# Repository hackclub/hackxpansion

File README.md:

<h1 align="center">
    Hackxpansion
</h1>

<h3 align="center">
    <a href="https://hackxpansion.koeg.dev">Website</a>
    <br/>
</h3>

<h4 align="center">
    A handheld console with 4 expansion solts
</h4>

<div align="center">
    
</div>

## Key Features

- Resistor based module identification at start up
- [2" 240x320 ST7789 LCD panel](https://www.buydisplay.com/2-inch-ips-tft-lcd-display-ips-panel-screen-240x320-for-smart-watch)
- RP2354 MCU
- Easily adaptable [module standard](https://hackxpansion.dino.icu/docs/detailed/card)
- Rust firmware with [embassy](https://embassy.dev/) and [slint-ui](https://slint.dev/)

## Why?

I really like the idea of modules, and modular things, and making people work together, so I made this.

## PCB

The console has two 4 layer PCBs designed in KiCAD, a main-board and a daughter-board, designed for JLC's basic process. 

### Main-Board

### Daughter-Board

## Making Your Own Modules

There are three simple steps to making your own module:

1. Design the module PCB in KiCAD
2. Design the module case in CAD
3. Write a driver for the module

There are detailed docs on the [hackxpansion website](https://hackxpansion.dino.icu/docs)

## Case

The case is designed in Autodesk Fusion, there are .f3z files in the hardware directory.

The models have parameters that can be adjusted to fit your needs.

## Shoutouts

Thank you so much for [Simon](https://github.com/NEOgHacking) who helped with the fanout of the RP, and also gave a ton of constructive feedback!!!!

## Zine

## BOM for Console

This is for an order of 2 PCBA PCBs.

Also found in a [CSV file](hardware/hackxpansion/BOM.csv). Each component has an LCSC part number attached that can be used to find the component on the LCSC website.

|Item                      |Price per unit|Nr of units|Total price|Link                                                                                          |
|--------------------------|--------------|-----------|-----------|----------------------------------------------------------------------------------------------|
|PCB with PCBA             |$60.00        |1          |$60.00     |https://jlcpcb.com/                                                                           |
|Display                   |$4.36         |1          |$4.36      |https://www.buydisplay.com/2-inch-ips-tft-lcd-display-ips-panel-screen-240x320-for-smart-watch|
|2x7 2.54mm header         |$0.386        |10         |$3.860     |https://www.aliexpress.com/item/1005012166781874.html                                         |
|Battery 502035            |$6.64         |1          |$6.64      |https://www.aliexpress.com/item/1005008218024646.html                                         |
|M2 OD3 L2 heat set insert |$0.0696       |15         |$1.0440    |https://www.aliexpress.com/item/1005006798286851.html                                         |
|M2 L6 screw               |$0.0766       |5          |$0.3830    |https://www.aliexpress.com/item/4000970993800.html                                            |
|M2 L8 screw               |$0.0766       |2          |$0.1532    |https://www.aliexpress.com/item/4000970993800.html                                            |
|M2 L4 screw               |$0.0766       |8          |$0.6128    |https://www.aliexpress.com/item/4000970993800.html                                            |
|                          |              |Total:     |$77.05     |                                                                                              |

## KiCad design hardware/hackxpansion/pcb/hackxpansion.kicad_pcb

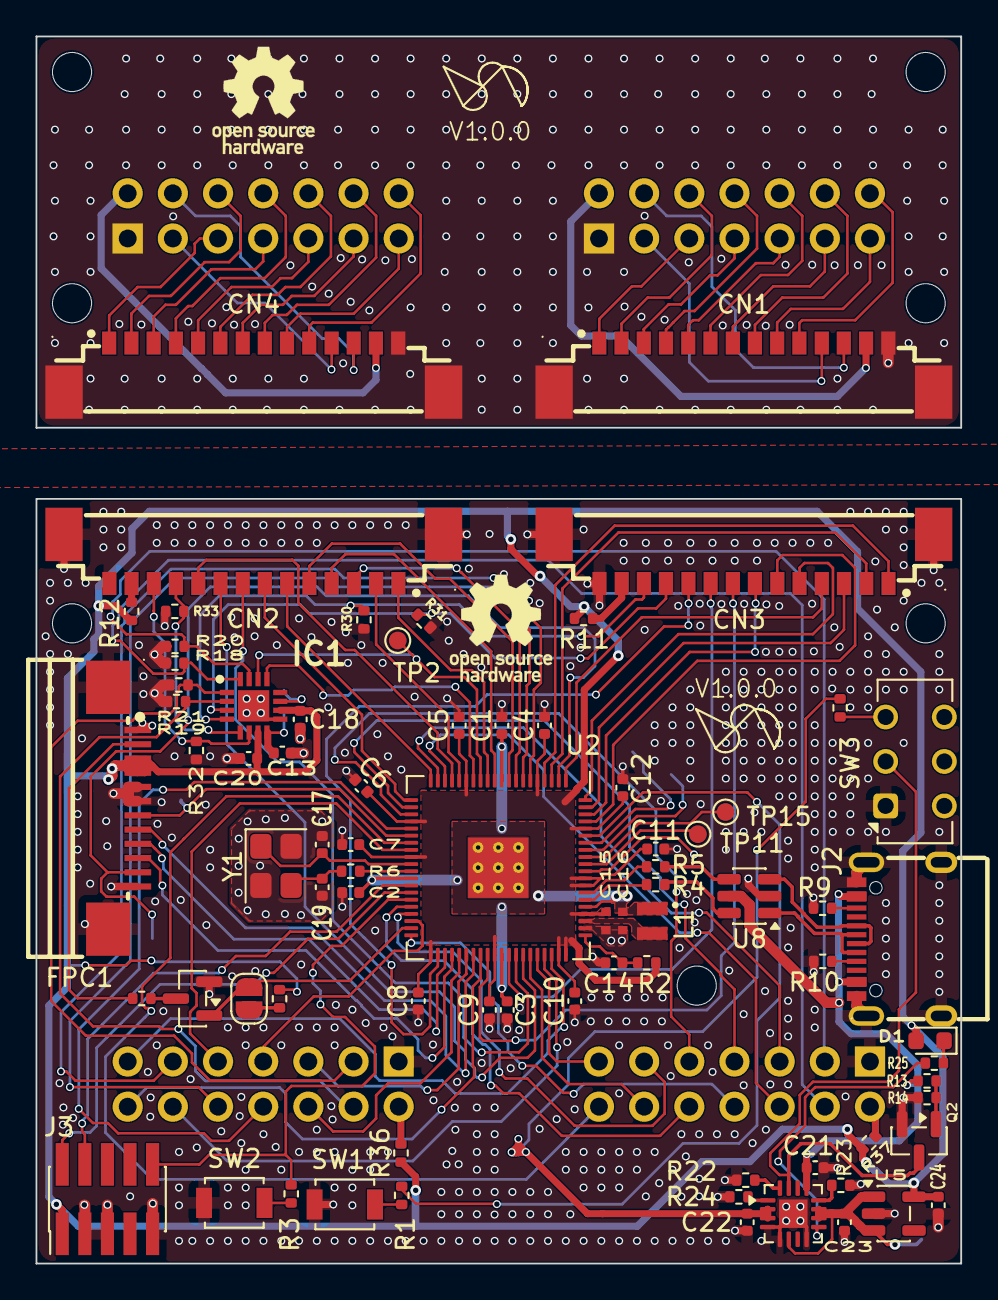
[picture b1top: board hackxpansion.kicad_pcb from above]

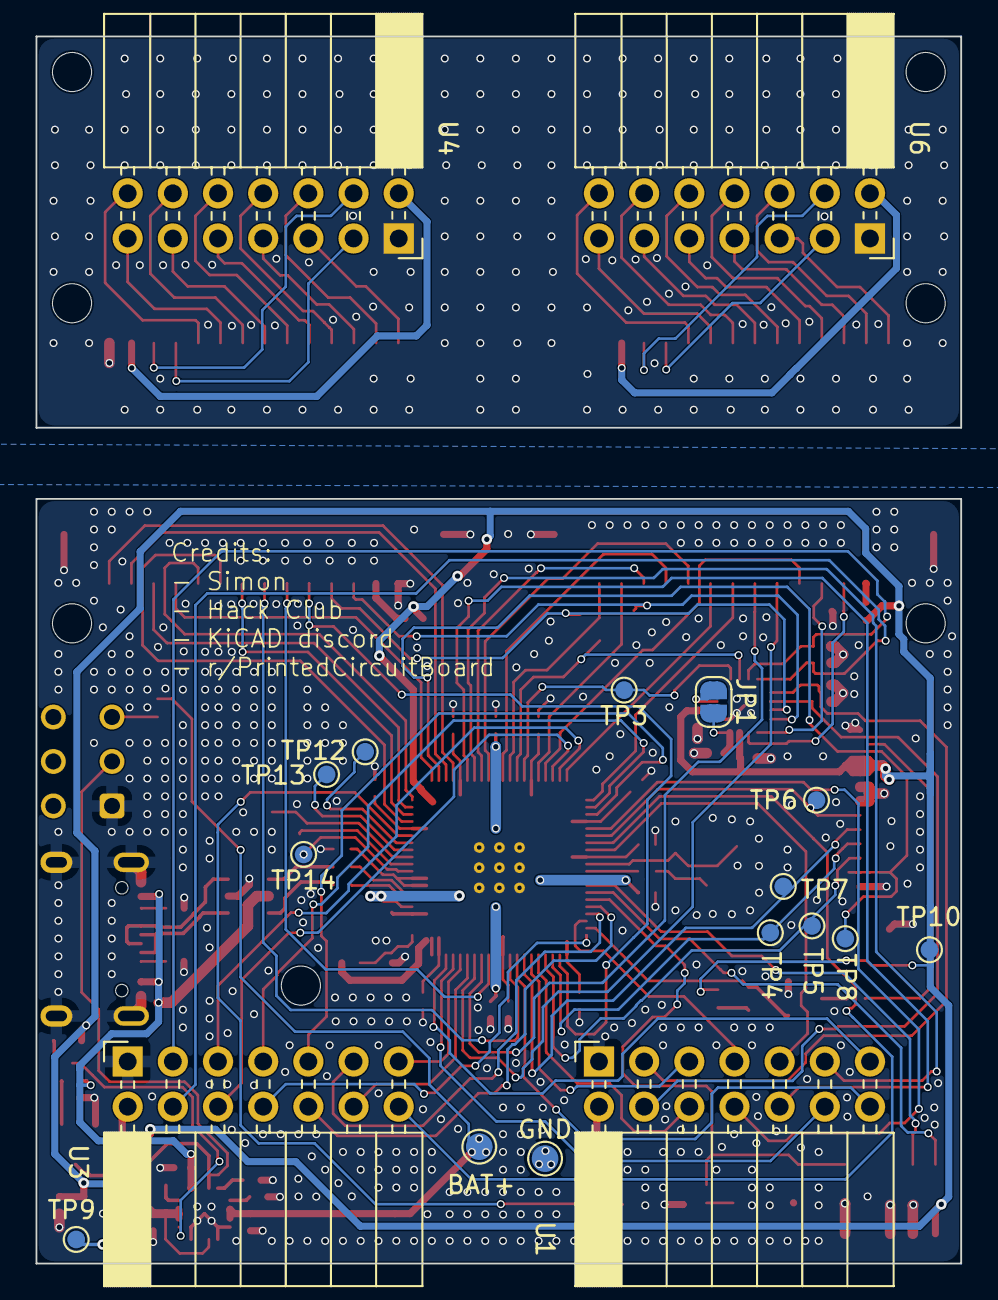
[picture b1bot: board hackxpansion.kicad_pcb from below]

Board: 4 copper layers, 52.0 x 43.0 mm, 104 parts (21 on the bottom side), 130 nets.

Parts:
BAT+: TestPoint; TestPoint_Pad_D1.5mm
C1, C3, C4, C5, C6, C7, C8, C9, C10, C11, C12: 100n; C_0402_1005Metric
C2, C14, C21, C22, C23, C24: 4u7; C_0402_1005Metric
C13, C18, C20: 1u; C_0402_1005Metric
C15, C16: 4u7; C_0402_1005Metric_small_pads
C17, C19: 15p; C_0402_1005Metric
CN1, CN2, CN3, CN4: 533981471; CONN-SMD_14P-P1.25_MOLEX_533981471
D1: LED; LED_0603_1608Metric
FPC1: AFC08-S12ECA-00; FPC-SMD_P0.80-12P_LCS-SJ-H2.0
GND: TestPoint; TestPoint_Pad_D1.5mm
H1, H2, H3, H4, H5, H6, H7: MountingHole; MountingHole_2.2mm_M2
IC1: ADS7128IRTET; QFN50P300X300X80-17N-D
J2: USB_C_Receptacle_USB2.0_14P; USB-C-SMD_TYPE-C-16PIN-2MD-073
J3: Conn_ARM_JTAG_SWD_10; PinHeader_2x05_P1.27mm_Vertical_SMD
JP1, JP3: SolderJumper_2_Open; SolderJumper-2_P1.3mm_Open_RoundedPad1.0x1.5mm
L1: 3u3; L_pol_2016
Q1: BSS138; SOT-23
Q2: 2N7002; SOT-23
R1, R3, R6: 1k; R_0402_1005Metric
R2: 33R; R_0402_1005Metric
R4, R5: 27R; R_0402_1005Metric
R7: 10R; R_0402_1005Metric
R8, R14, R18, R19, R20, R21, R24, R30, R31, R32, R33: 10k; R_0402_1005Metric
R9, R10: 5k1; R_0402_1005Metric
R11, R12, R36, R37: 5R1; R_0402_1005Metric
R13: 100R; R_0402_1005Metric
R15: 100k; R_0402_1005Metric
R22: 3k3; R_0402_1005Metric
R23, R25: 1k5; R_0402_1005Metric
SW1, SW2: SW_Push; SW_SPST_B3U-1000P
SW3: SW_On_Off; SW_CK_JS202011AQN_DPDT_Angled
SYM1, SYM2: Logo_Open_Hardware_Small; OSHW-Logo_5.7x6mm_SilkScreen
TP2, TP3, TP4, TP5, TP6, TP7, TP8, TP9, TP10, TP11, TP12, TP13, TP14, TP15: TestPoint; TestPoint_Pad_D1.0mm
U1, U3, U4, U6: PinSocket_2x07_P2.54mm_Horizontal
U2: RP2354B; RP2350-QFN-80-1EP_10x10_P0.4mm_EP3.4x3.4mm_ThermalVias
U5: SPX3819M5-L-3-3; SOT-23-5
U7: BQ24075RGT; VQFN-16-1EP_3x3mm_P0.5mm_EP1.6x1.6mm
U8: USBLC6-2SC6; SOT-23-6
Y1: ABM8-272-T3; Crystal_SMD_3225-4Pin_3.2x2.5mm

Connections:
+1V1: C1.1, C2.1, C3.1, C16.1, L1.1, U2.10 (DVDD), U2.32 (DVDD), U2.51 (DVDD), U2.65 (VREG_FB)
/+3V3: C4.1, C5.1, C6.1, C7.1, C8.1, C9.1, C10.1, C11.1, C12.1, C15.1, C18.1, C20.1, C24.2, D1.2 (A), FPC1.3, FPC1.4, IC1.7 (AVDD), IC1.10 (DVDD), J3.1 (VTref), R2.1, R8.2, R11.1, R12.1, R36.1, R37.1, TP10.1 (1_1), U2.5 (IOVDD), U2.15 (IOVDD), U2.24 (IOVDD), U2.29 (IOVDD), U2.41 (IOVDD), U2.50 (IOVDD), U2.59 (ADC_AVDD), U2.60 (IOVDD), U2.64 (VREG_VIN), U2.68 (USB_OTP_VDD), U2.69 (QSPI_IOVDD), U2.76 (IOVDD), U5.5 (OUT)
/Connector Daughter Mod2/bank.GPIO0: CN1.1, U4.5 (GPIO0)
/Connector Daughter Mod2/bank.GPIO1: CN1.2, U4.6 (GPIO1)
/Connector Daughter Mod2/bank.GPIO2: CN1.3, U4.7 (GPI02)
/Connector Daughter Mod2/bank.GPIO3: CN1.4, U4.8 (GPIO3)
/Connector Daughter Mod2/bank.GPIO4: CN1.5, U4.9 (GPIO4)
/Connector Daughter Mod2/bank.GPIO5: CN1.6, U4.10 (GPIO5)
/Connector Daughter Mod2/bank.GPIO6: CN1.7, U4.11 (GPIO6)
/Connector Daughter Mod2/bank.GPIO7: CN1.8, U4.12 (GPIO7)
/Connector Daughter Mod2/bank.GPIO8: CN1.9, U4.13 (GPIO8)
/Connector Daughter Mod2/bank.GPIO9: CN1.10, U4.14 (GPIO9)
/Connector Daughter Mod2/mod.MD0: CN1.11, U4.3 (MD0)
/Connector Daughter Mod2/mod.MD1: CN1.12, U4.4 (MD1)
/Connector Daughter Mod3/bank.GPIO0: CN4.1, U6.5 (GPIO0)
/Connector Daughter Mod3/bank.GPIO1: CN4.2, U6.6 (GPIO1)
/Connector Daughter Mod3/bank.GPIO2: CN4.3, U6.7 (GPI02)
/Connector Daughter Mod3/bank.GPIO3: CN4.4, U6.8 (GPIO3)
/Connector Daughter Mod3/bank.GPIO4: CN4.5, U6.9 (GPIO4)
/Connector Daughter Mod3/bank.GPIO5: CN4.6, U6.10 (GPIO5)
/Connector Daughter Mod3/bank.GPIO6: CN4.7, U6.11 (GPIO6)
/Connector Daughter Mod3/bank.GPIO7: CN4.8, U6.12 (GPIO7)
/Connector Daughter Mod3/bank.GPIO8: CN4.9, U6.13 (GPIO8)
/Connector Daughter Mod3/bank.GPIO9: CN4.10, U6.14 (GPIO9)
/Connector Daughter Mod3/mod.MD0: CN4.11, U6.3 (MD0)
/Connector Daughter Mod3/mod.MD1: CN4.12, U6.4 (MD1)
/Connector Main Mod2/+3V3: CN3.13, R11.2
/Connector Main Mod2/bank.GPIO0: CN3.1, U2.4 (GPIO7)
/Connector Main Mod2/bank.GPIO1: CN3.2, U2.3 (GPIO6)
/Connector Main Mod2/bank.GPIO2: CN3.3, U2.79 (GPIO2)
/Connector Main Mod2/bank.GPIO3: CN3.4, U2.1 (GPIO4)
/Connector Main Mod2/bank.GPIO4: CN3.5, U2.80 (GPIO3)
/Connector Main Mod2/bank.GPIO5: CN3.6, U2.77 (GPIO0)
/Connector Main Mod2/bank.GPIO6: CN3.7, U2.78 (GPIO1)
/Connector Main Mod2/bank.GPIO7: CN3.8, U2.49 (GPIO40/ADC0)
/Connector Main Mod2/bank.GPIO8: CN3.9, U2.52 (GPIO41/ADC1)
/Connector Main Mod2/bank.GPIO9: CN3.10, U2.42 (GPIO33)
/Connector Main Mod2/mod.MD0: CN3.11, IC1.3 (AIN4/GPIO4), R31.1
/Connector Main Mod2/mod.MD1: CN3.12, IC1.4 (AIN5/GPIO5), R30.1
/Connector Main Mod3/+3V3: CN2.13, R12.2
/Connector Main Mod3/bank.GPIO0: CN2.1, U2.12 (GPIO13)
/Connector Main Mod3/bank.GPIO1: CN2.2, U2.16 (GPIO16)
/Connector Main Mod3/bank.GPIO2: CN2.3, U2.8 (GPIO10)
/Connector Main Mod3/bank.GPIO3: CN2.4, U2.11 (GPIO12)
/Connector Main Mod3/bank.GPIO4: CN2.5, U2.9 (GPIO11)
/Connector Main Mod3/bank.GPIO5: CN2.6, U2.20 (GPIO20)
/Connector Main Mod3/bank.GPIO6: CN2.7, U2.21 (GPIO21)
/Connector Main Mod3/bank.GPIO7: CN2.8, U2.53 (GPIO42/ADC2)
/Connector Main Mod3/bank.GPIO8: CN2.9, U2.54 (GPIO43/ADC3)
/Connector Main Mod3/bank.GPIO9: CN2.10, U2.17 (GPIO17)
/Connector Main Mod3/mod.MD0: CN2.11, IC1.5 (AIN6/GPIO6), R33.1
/Connector Main Mod3/mod.MD1: CN2.12, IC1.6 (AIN7/GPIO7), R32.1
/DAUGHT_GND: CN1.14, CN1.15, CN1.16, CN4.14, CN4.15, CN4.16, U4.1 (GND), U6.1 (GND)
/Daughter Board/+3V3_MOD2: CN1.13, U4.2 (3V3)
/Daughter Board/+3V3_MOD3: CN4.13, U6.2 (3V3)
/GND: C1.2, C2.2, C3.2, C4.2, C5.2, C6.2, C7.2, C8.2, C9.2, C10.2, C11.2, C12.2, C13.2, C14.2, C15.2, C16.2, C17.1, C18.2, C19.1, C20.2, C21.1, C22.1, C23.1, C24.1, CN2.14, CN2.15, CN2.16, CN3.14, CN3.15, CN3.16, FPC1.1, FPC1.5, FPC1.6, FPC1.12, FPC1.13, FPC1.14, GND.1 (1_1), IC1.9 (GND), IC1.17 (EP), J2.A1 (GND), J2.A12 (GND), J2.B1 (GND), J2.B12 (GND), J2.SH (SHIELD), J3.3 (GND), J3.5 (GND), J3.9 (GNDDetect), Q1.2 (S), Q2.2 (S), R9.2, R10.2, R14.2, R18.2, R19.2, R20.2, R21.2, R22.2, R23.2, R24.2, R30.2, R31.2, R32.2, R33.2, SW1.1, SW2.1, SW3.1 (A), U1.1 (GND), U2.62 (VREG_PGND), U2.81 (GND), U3.1 (GND), U5.2 (GND), U7.4 (~CE), U7.5 (EN2), U7.8 (VSS), U7.17 (VSS), U8.2 (GND), Y1.2 (G), Y1.4 (G)
/Main Board/ADC/SCL: IC1.13 (SCL), TP3.1 (1_1), U2.14 (GPIO15)
/Main Board/ADC/SDA: IC1.14 (SDA), TP2.1 (1_1), U2.13 (GPIO14)
/Main Board/ADC/mod0.MD0: IC1.1 (AIN2/GPIO2), R21.1, U1.3 (MD0)
/Main Board/ADC/mod0.MD1: IC1.2 (AIN3/GPIO3), R19.1, U1.4 (MD1)
/Main Board/ADC/mod1.MD0: IC1.15 (AIN0/GPIO0), R20.1, U3.3 (MD0)
/Main Board/ADC/mod1.MD1: IC1.16 (AIN1/GPIO1), R18.1, U3.4 (MD1)
/Main Board/Display/BACKLIGHT: JP3.2 (B), Q1.1 (G), U2.39 (GPIO31)
/Main Board/Display/CS: FPC1.8, TP7.1 (1_1), U2.47 (GPIO38)
/Main Board/Display/DC: FPC1.7, TP6.1 (1_1), U2.26 (GPIO25)
/Main Board/Display/MOSI: FPC1.10, TP5.1 (1_1), U2.44 (GPIO35)
/Main Board/Display/RESET: FPC1.11, TP8.1 (1_1), U2.2 (GPIO5)
/Main Board/Display/SCLK: FPC1.9, TP4.1 (1_1), U2.43 (GPIO34)
/Main Board/Module Bay 0/+3V3: R36.2, U1.2 (3V3)
/Main Board/Module Bay 0/GPIO0: U1.5 (GPIO0), U2.46 (GPIO37)
/Main Board/Module Bay 0/GPIO1: U1.6 (GPIO1), U2.45 (GPIO36)
/Main Board/Module Bay 0/GPIO2: U1.7 (GPI02), U2.38 (GPIO30)
/Main Board/Module Bay 0/GPIO3: U1.8 (GPIO3), U2.25 (GPIO24)
/Main Board/Module Bay 0/GPIO4: U1.9 (GPIO4), U2.28 (GPIO27)
/Main Board/Module Bay 0/GPIO5: U1.10 (GPIO5), U2.6 (GPIO8)
/Main Board/Module Bay 0/GPIO6: U1.11 (GPIO6), U2.7 (GPIO9)
/Main Board/Module Bay 0/GPIO7: U1.12 (GPIO7), U2.57 (GPIO46/ADC6)
/Main Board/Module Bay 0/GPIO8: U1.13 (GPIO8), U2.58 (GPIO47/ADC7)
/Main Board/Module Bay 0/GPIO9: U1.14 (GPIO9), U2.48 (GPIO39)
/Main Board/Module Bay 1/+3V3: R37.2, U3.2 (3V3)
/Main Board/Module Bay 1/GPIO0: U2.19 (GPIO19), U3.5 (GPIO0)
/Main Board/Module Bay 1/GPIO1: U2.18 (GPIO18), U3.6 (GPIO1)
/Main Board/Module Bay 1/GPIO2: U2.22 (GPIO22), U3.7 (GPI02)
/Main Board/Module Bay 1/GPIO3: U2.40 (GPIO32), U3.8 (GPIO3)
/Main Board/Module Bay 1/GPIO4: U2.23 (GPIO23), U3.9 (GPIO4)
/Main Board/Module Bay 1/GPIO5: U2.36 (GPIO28), U3.10 (GPIO5)
/Main Board/Module Bay 1/GPIO6: U2.37 (GPIO29), U3.11 (GPIO6)
/Main Board/Module Bay 1/GPIO7: U2.55 (GPIO44/ADC4), U3.12 (GPIO7)
/Main Board/Module Bay 1/GPIO8: U2.56 (GPIO45/ADC5), U3.13 (GPIO8)
/Main Board/Module Bay 1/GPIO9: U2.27 (GPIO26), U3.14 (GPIO9)
/Main Board/Power/+BATT: BAT+.1 (1_1), C22.2, R15.1, U7.2 (BAT), U7.3 (BAT)
/Main Board/Power/ILIM: R23.1, U7.12 (ILIM)
/Main Board/Power/ISET: R22.1, U7.16 (ISET)
/Main Board/Power/REG-OUT: C23.2, TP9.1 (1_1), U5.1 (IN), U5.3 (EN), U7.6 (EN1), U7.10 (OUT), U7.11 (OUT)
/Main Board/Power/SYSOFF: Q2.3 (D), SW3.2 (B), U7.15 (SYSOFF)
/Main Board/Power/TS: R24.1, U7.1 (TS)
/Main Board/Power/VBUS: C21.2, J2.A4 (VBUS), J2.A9 (VBUS), J2.B4 (VBUS), J2.B9 (VBUS), R13.1, U7.13 (IN), U8.5 (VBUS)
/Main Board/RP2354B/D+: R5.1, U8.4 (I/O2)
/Main Board/RP2354B/D-: R4.1, U8.6 (I/O1)
/Main Board/RP2354B/QSPI_SS: R1.2, U2.75 (~QSPI_SS)
/Main Board/RP2354B/RUN: J3.10 (~RESET), R3.2, U2.35 (RUN)
/Main Board/RP2354B/SWCLK: J3.4 (SWCLK/TCK), U2.33 (SWCLK)
/Main Board/RP2354B/SWDIO: J3.2 (SWDIO/TMS), U2.34 (SWDIO)
/Main Board/RP2354B/~USB_BOOT: R1.1, SW1.2
/Main Board/USB/CC1: J2.A5 (CC1), R10.1
/Main Board/USB/CC2: J2.B5 (CC2), R9.1
/Main Board/USB/DIRTY_D+: J2.A6 (D+), J2.B6 (D+), U8.3 (I/O2)
/Main Board/USB/DIRTY_D-: J2.A7 (D-), J2.B7 (D-), U8.1 (I/O1)
unnamed: C19.2, R6.1, Y1.3
unnamed: D1.1 (K), R25.1
unnamed: FPC1.2, R7.2
unnamed: IC1.11 (ADDR), JP1.1 (A)
unnamed: C13.1, IC1.8 (DECAP), JP1.2 (B)
unnamed: JP3.1 (A), R8.1
unnamed: Q1.3 (D), R7.1
unnamed: Q2.1 (G), R13.2, R14.1
unnamed: R3.1, SW2.2
unnamed: R15.2, SW3.3 (C)
unnamed: TP11.1 (1_1), U2.71 (QSPI_SCLK)
unnamed: TP15.1 (1_1), U2.72 (QSPI_SD0)
unnamed: TP12.1 (1_1), U2.74 (QSPI_SD1)
unnamed: TP13.1 (1_1), U2.73 (QSPI_SD2)
unnamed: TP14.1 (1_1), U2.70 (QSPI_SD3)
unnamed: R4.2, U2.66 (USB_DM)
unnamed: R5.2, U2.67 (USB_DP)
unnamed: C14.1, R2.2, U2.61 (VREG_AVDD)
unnamed: L1.2, U2.63 (VREG_LX)
unnamed: C17.2, U2.30 (XIN), Y1.1
unnamed: R6.2, U2.31 (XOUT)
unnamed: R25.2, U7.9 (~CHG)

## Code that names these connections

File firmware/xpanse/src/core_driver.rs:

use xpanse_api::gpio_bank::GpioBank;
use xpanse_api::registry::Registry;

use crate::load_driver::load_driver_pair;
use crate::{adc::init_adc, adc_mapping, resource_split::*};
use xpanse_api::bus::allocator::BusAllocator;
use xpanse_api::interfaces::adc;
use xpanse_api::interfaces::usb::UsbPeripheral;
use xpanse_api::metadata::{ModuleID, ModuleSlot};

use embassy_sync::{blocking_mutex::raw::CriticalSectionRawMutex, signal::Signal};
use embassy_time::{Duration, Timer, with_timeout};

const MODULE_DETECTION_TIMEOUT: Duration = Duration::from_millis(100);

macro_rules! gpio_bank_from_peris {
    ($peri:expr) => {
        GpioBank::new(
            $peri.gpio0,
            $peri.gpio1,
            $peri.gpio2,
            $peri.gpio3,
            $peri.gpio4,
            $peri.gpio5,
            $peri.gpio6,
            $peri.gpio7,
            $peri.gpio8,
            $peri.gpio9,
            $peri.pwm_slice1,
            $peri.pwm_slice2,
            $peri.pwm_slice3,
        )
    };
}

static REGISTRY_HANDOFF: Signal<CriticalSectionRawMutex, Registry> = Signal::new();

pub async fn take_registry() -> Registry {
    REGISTRY_HANDOFF.wait().await
}

#[embassy_executor::task]
pub async fn app_core_task(
    gpio_bank_0: GpioBankPeris0,
    gpio_bank_1: GpioBankPeris1,
    gpio_bank_2: GpioBankPeris2,
    gpio_bank_3: GpioBankPeris3,
    mut i2c_pins: I2cPinPeris,
    remaining_peris: RemainingPeris,
) {
    defmt::info!("app_core: started on core 1");

    let gpio_bank_0 = gpio_bank_from_peris!(gpio_bank_0);
    let gpio_bank_1 = gpio_bank_from_peris!(gpio_bank_1);
    let gpio_bank_2 = gpio_bank_from_peris!(gpio_bank_2);
    let gpio_bank_3 = gpio_bank_from_peris!(gpio_bank_3);
    defmt::info!("app_core: GPIO banks initialized");

    defmt::info!("app_core: initializing module-detection ADC");
    let module_ids = {
        let module_adc = match init_adc(i2c_pins.sda.reborrow(), i2c_pins.scl.reborrow()).await {
            Ok(adc) => {
                defmt::info!("app_core: module-detection ADC initialized");
                Some(adc)
            }
            Err(error) => {
                defmt::error!(
                    "app_core: module-detection ADC initialization failed: {:?}",
                    error
                );
                None
            }
        };

        match module_adc {
            Some(mut module_adc) => {
                let front_right = detect_module(&mut module_adc, ModuleSlot::FrontRight).await;
                let front_left = detect_module(&mut module_adc, ModuleSlot::FrontLeft).await;
                let back_right = detect_module(&mut module_adc, ModuleSlot::BackRight).await;
                let back_left = detect_module(&mut module_adc, ModuleSlot::BackLeft).await;
                [front_right, front_left, back_right, back_left]
            }
            None => [None; 4],
        }
    };

    defmt::info!("app_core: initializing internal ADC");
    adc::init_adc(remaining_peris.adc, remaining_peris.adc_temp);
    defmt::info!("app_core: internal ADC initialized");

    defmt::info!("app_core: creating bus allocator");
    let mut bus_allocator = BusAllocator::new(
        None,
        Some(remaining_peris.spi1),
        Some(remaining_peris.i2c0),
        Some(remaining_peris.i2c1),
        Some(remaining_peris.uart0),
        Some(remaining_peris.uart1),
        xpanse_api::bus::allocator::DmaPool {
            ch0: Some(remaining_peris.dma_ch0),
            ch1: Some(remaining_peris.dma_ch1),
            ch2: Some(remaining_peris.dma_ch2),
            ch3: Some(remaining_peris.dma_ch3),
            ch4: Some(remaining_peris.dma_ch4),
            ch5: Some(remaining_peris.dma_ch5),
            ch6: Some(remaining_peris.dma_ch6),
            ch7: Some(remaining_peris.dma_ch7),
            ch8: Some(remaining_peris.dma_ch8),
            ch9: Some(remaining_peris.dma_ch9),
            ch10: Some(remaining_peris.dma_ch10),
            ch11: Some(remaining_peris.dma_ch11),
            ch12: Some(remaining_peris.dma_ch12),
            ch13: Some(remaining_peris.dma_ch13),
            ch14: Some(remaining_peris.dma_ch14),
            ch15: Some(remaining_peris.dma_ch15),
        },
        remaining_peris.pio0,
        remaining_peris.pio1,
        remaining_peris.pio2,
    );

    let mut registry = Registry::new();
    registry.register_platform::<UsbPeripheral>(remaining_peris.usb);

    defmt::info!("app_core: loading module drivers");
    load_driver_pair(
        (
            (module_ids[0], gpio_bank_0, ModuleSlot::FrontRight),
            (module_ids[1], gpio_bank_1, ModuleSlot::FrontLeft),
        ),
        &mut registry,
        &mut bus_allocator,
    )
    .await;
    load_driver_pair(
        (
            (module_ids[2], gpio_bank_2, ModuleSlot::BackRight),
            (module_ids[3], gpio_bank_3, ModuleSlot::BackLeft),
        ),
        &mut registry,
        &mut bus_allocator,
    )
    .await;

    defmt::info!("app_core: drivers loaded, handing registry to core 0");
    REGISTRY_HANDOFF.signal(registry);
}

async fn detect_module(adc: &mut crate::adc::Adc<'_>, slot: ModuleSlot) -> Option<ModuleID> {
    defmt::info!("app_core: detecting module in {:?}", slot);

    for attempt in 1..=3 {
        match with_timeout(MODULE_DETECTION_TIMEOUT, adc_mapping::map_adc(adc, slot)).await {
            Ok(Ok(Some(id))) => {
                defmt::info!("app_core: detected module {:?} in {:?}", id, slot);
                return Some(id);
            }
            Ok(Ok(None)) => {
                defmt::info!("app_core: no module detected in {:?}", slot);
                return None;
            }
            Ok(Err(error)) => defmt::warn!(
                "app_core: module detection attempt {} failed for {:?}: {:?}",
                attempt,
                slot,
                error
            ),
            Err(_) => defmt::warn!(
                "app_core: module detection attempt {} timed out for {:?}",
                attempt,
                slot
            ),
        }
        Timer::after_millis(10).await;
    }
    defmt::error!("app_core: module detection failed for {:?}", slot);
    None
}
